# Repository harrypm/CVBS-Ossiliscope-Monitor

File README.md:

# CVBS-Oscilloscope-Monitor

This repository is a KiCAD transcription of a circuit by Alan Wolfe.

## Description

The following circuit converts a composite signal and splits the signal as such that it can display video on analog-style oscilloscopes using X,Y & Z inputs.

## Features

- LED indicator - Used for monitoring power
- Power jacks/pads - choice between barrel jack or 3.96mm headers
- BNC connectors for inputs and outputs

- 2 flexable versions depending on users needs

## [THT](CVBS-Ossiliscope-Monitor/Releases/THT) Through Hole (Hand Soldering Version)

This version is simmaller to the equipmnet its intended to be used with as every single part is hand user replaceable simply fabricate the bare boards and order the parts acording the to BOM list.

## [SMD](CVBS-Ossiliscope-Monitor/Releases/SMD) Surface Mount (Factory Frabrication Version)

This version following modern fabrication standards is intended for ease of automated fabraication allowing drag and drop 1-2-3 ordering from services like PCBway or JLCPCB.

## Additional information

Links :

* [PDF link](https://www.qsl.net/w2aew/W2AEW_NTSC_to_scope.pdf)
* [Youtube](https://www.youtube.com/watch?v=yf4kOMSPbM0&start=55)

## Credits

Transcription - Charles Garcia [@cgarcia2097](https://github.com/cgarcia2097)

Orignal Circuit - Alan Wolfe [PDF link](https://www.qsl.net/w2aew/W2AEW_NTSC_to_scope.pdf)

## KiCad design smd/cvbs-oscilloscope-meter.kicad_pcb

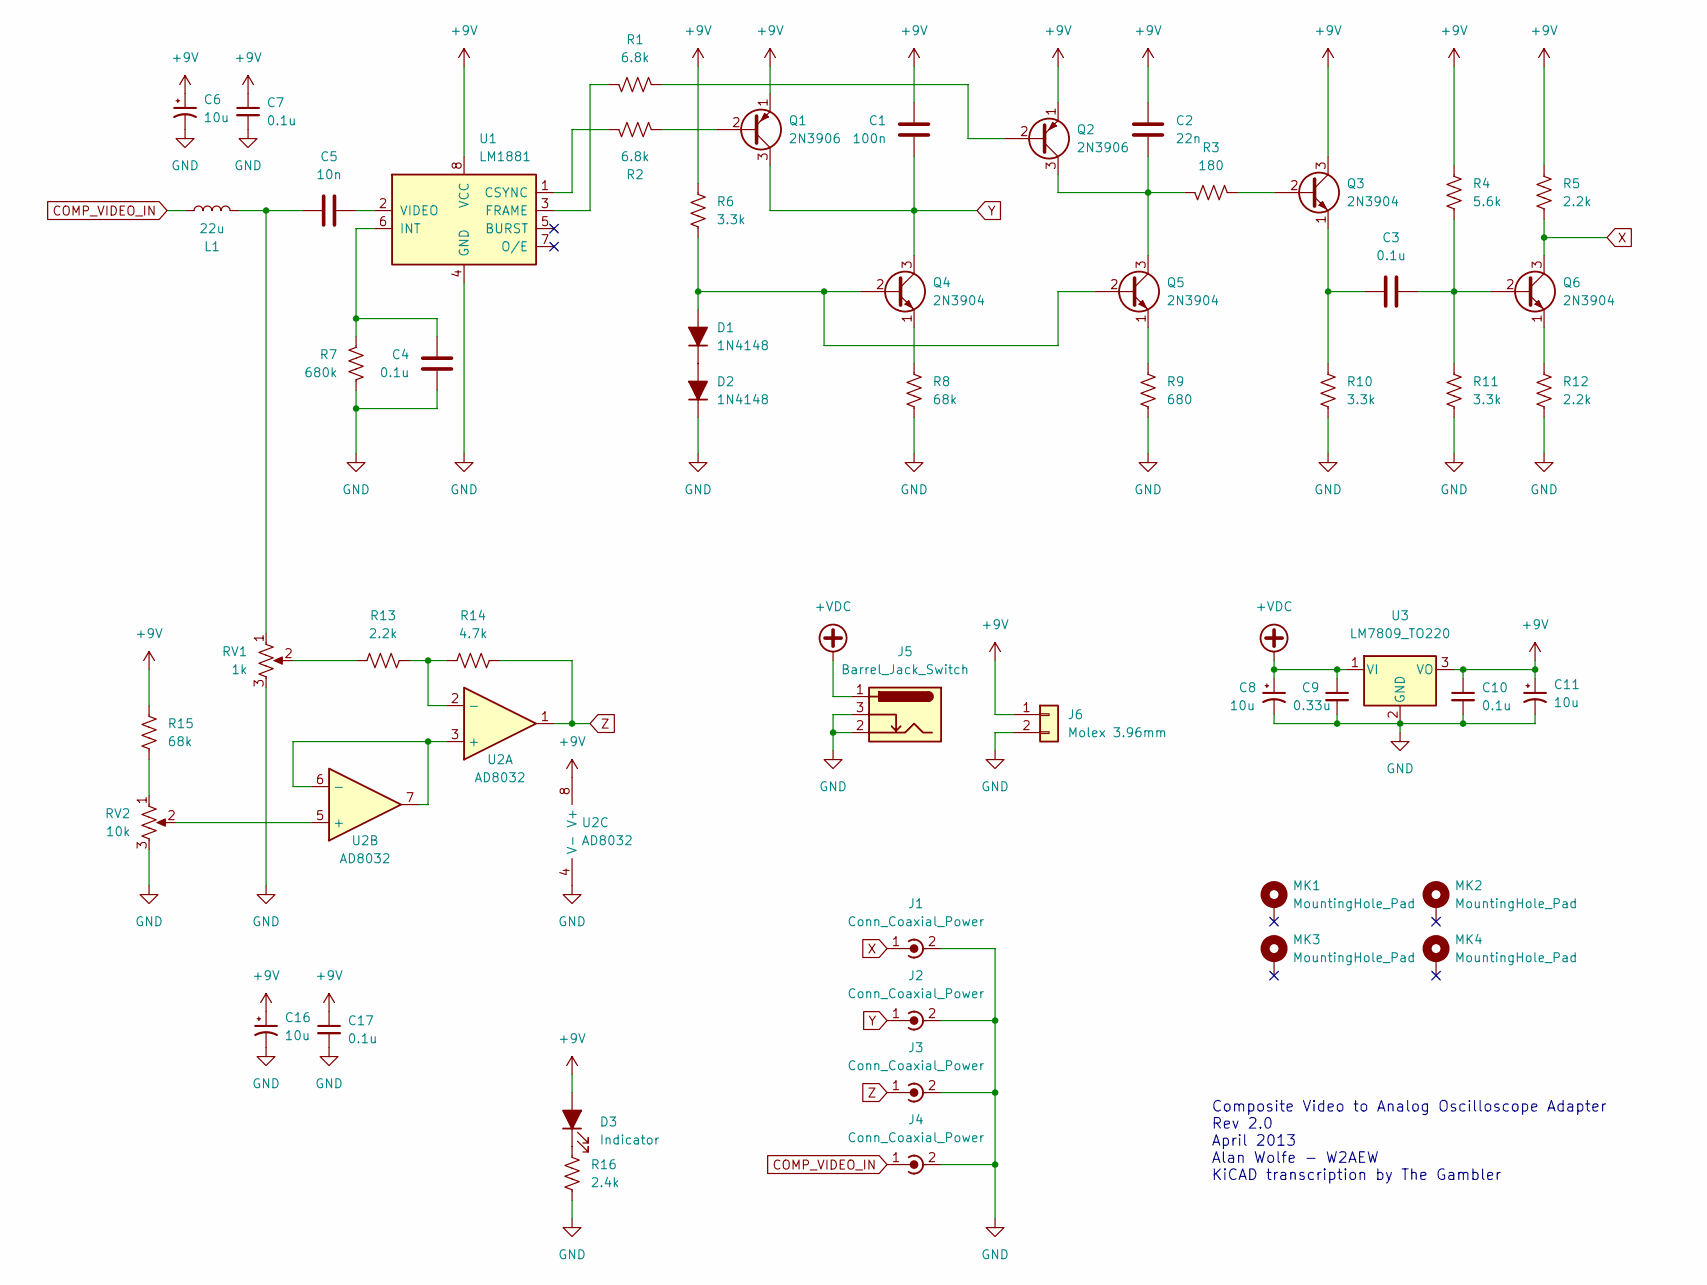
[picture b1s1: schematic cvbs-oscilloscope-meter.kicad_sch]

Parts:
C1: 100n; C_0805_2012Metric_Pad1.18x1.45mm_HandSolder
C2: 22n; C_0805_2012Metric_Pad1.18x1.45mm_HandSolder
C3, C4, C7, C10, C17: 0.1u; C_0805_2012Metric_Pad1.18x1.45mm_HandSolder
C5: 10n; C_0805_2012Metric_Pad1.18x1.45mm_HandSolder
C6, C8, C11, C16: 10u; CP_Elec_5x5.9
C9: 0.33u; C_0805_2012Metric_Pad1.18x1.45mm_HandSolder
D1, D2: 1N4148; D_SOD-123
D3: Indicator; LED_0805_2012Metric_Pad1.15x1.40mm_HandSolder
J1, J2, J3, J4: Conn_Coaxial_Power; BNC_TEConnectivity_1478035_Horizontal
J5: Barrel_Jack_Switch; BarrelJack_GCT_DCJ200-10-A_Horizontal
J6: Molex 3.96mm; Molex_KK-396_A-41791-0002_1x02_P3.96mm_Vertical
L1: 22u; L_10.4x10.4_H4.8
MK1, MK2, MK3, MK4: MountingHole_Pad; MountingHole_3.2mm_M3_DIN965
Q1, Q2: 2N3906; SOT-23
Q3, Q4, Q5, Q6: 2N3904; SOT-23
R1, R2: 6.8k; R_0805_2012Metric_Pad1.20x1.40mm_HandSolder
R3: 180; R_0805_2012Metric_Pad1.20x1.40mm_HandSolder
R4: 5.6k; R_0805_2012Metric_Pad1.20x1.40mm_HandSolder
R5, R12, R13: 2.2k; R_0805_2012Metric_Pad1.20x1.40mm_HandSolder
R6, R10, R11: 3.3k; R_0805_2012Metric_Pad1.20x1.40mm_HandSolder
R7: 680k; R_0805_2012Metric_Pad1.20x1.40mm_HandSolder
R8, R15: 68k; R_0805_2012Metric_Pad1.20x1.40mm_HandSolder
R9: 680; R_0805_2012Metric_Pad1.20x1.40mm_HandSolder
R14: 4.7k; R_0805_2012Metric_Pad1.20x1.40mm_HandSolder
R16: 2.4k; R_0805_2012Metric_Pad1.20x1.40mm_HandSolder
RV1: 1k; Potentiometer_Piher_PC-16_Single_Vertical
RV2: 10k; Potentiometer_Piher_PC-16_Single_Vertical
U1: LM1881; SOIC-8-1EP_3.9x4.9mm_P1.27mm_EP2.29x3mm
U2: AD8032; SOIC-8-1EP_3.9x4.9mm_P1.27mm_EP2.29x3mm
U3: LM7809_TO220; SOT-223

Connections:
+9V: C1.2, C2.2, C6.1, C7.1, C10.1, C11.1, C16.1, C17.1, D3.2 (A), J6.1, Q1.1 (E), Q2.1 (E), Q3.3 (C), R4.1, R5.1, R6.1, R15.1, U1.8 (VCC), U2.8 (V+), U3.3 (VO)
+VDC: C8.1, C9.1, J5.1, U3.1 (VI)
COMP_VIDEO_IN: J4.1 (In), L1.1
GND: C4.1, C6.2, C7.2, C8.2, C9.2, C10.2, C11.2, C16.2, C17.2, D2.1 (K), J1.2 (Ext), J2.2 (Ext), J3.2 (Ext), J4.2 (Ext), J5.2, J5.3, J6.2, R7.1, R8.2, R9.2, R10.2, R11.2, R12.2, R16.2, RV1.3, RV2.3, U1.4 (GND), U2.4 (V-), U3.2 (GND)
unnamed: C2.1, Q2.3 (C), Q5.3 (C), R3.2
unnamed: C3.1, Q3.1 (E), R10.1
unnamed: C3.2, Q6.2 (B), R4.2, R11.1
unnamed: C4.2, R7.2, U1.6 (INT)
unnamed: C5.1, U1.2 (VIDEO)
unnamed: C5.2, L1.2, RV1.1
unnamed: D1.1 (K), D2.2 (A)
unnamed: D1.2 (A), Q4.2 (B), Q5.2 (B), R6.2
unnamed: D3.1 (K), R16.1
unnamed: Q1.2 (B), R2.2
unnamed: Q2.2 (B), R1.1
unnamed: Q3.2 (B), R3.1
unnamed: Q4.1 (E), R8.1
unnamed: Q5.1 (E), R9.1
unnamed: Q6.1 (E), R12.1
unnamed: R1.2, U1.3 (FRAME)
unnamed: R2.1, U1.1 (CSYNC)
unnamed: R13.1, RV1.2
unnamed: R13.2, R14.1, U2.2 (-)
unnamed: R15.2, RV2.1
unnamed: RV2.2, U2.5 (+)
unnamed: U2.3 (+), U2.6 (-), U2.7
X: J1.1 (In), Q6.3 (C), R5.2
Y: C1.1, J2.1 (In), Q1.3 (C), Q4.3 (C)
Z: J3.1 (In), R14.2, U2.1

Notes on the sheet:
Composite Video to Analog Oscilloscope Adapter Rev 2.0 April 2013 Alan Wolfe - W2AEW KiCAD transcription by The Gambler

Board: 2 copper layers, 54 parts (0 on the bottom side), 29 nets, no tracks yet.

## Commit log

2022-05-06 Created initial schematic
2022-05-07 Created schematic
2022-05-08 Created PCB
2022-05-08 Finished initial routing
    Finished Routing - will need to check and revise
2022-05-08 New update
    - Updated README
    - Added power and LED circuitry
2022-05-16 Created SMD boards
2022-05-16 Updated THT
    Starting new routing for new schematic layout
2022-05-24 Started PCB layout v2
2022-05-24 Simple index
2022-05-25 Finished routing
    Added routing
2022-06-01 Restruchering.
2022-06-04 Updated routing
    Updated routing
2022-06-15 Started PCB layout
    Started PCB layout
2022-06-20 Though Hole Release Version 1.0
